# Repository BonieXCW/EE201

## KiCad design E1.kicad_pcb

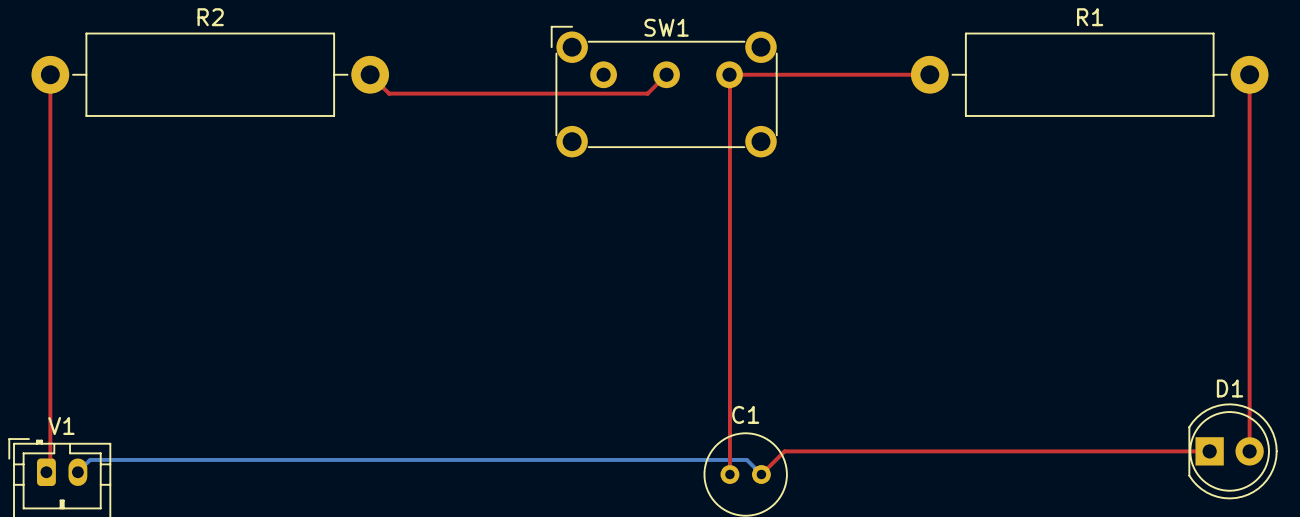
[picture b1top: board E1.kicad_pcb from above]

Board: 2 copper layers, 6 parts (0 on the bottom side), 5 nets.

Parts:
C1: 4.7 uF; C_Radial_D5.0mm_H5.0mm_P2.00mm
D1: LED; LED_D5.0mm
R1: 20 kohms; R_Axial_DIN0516_L15.5mm_D5.0mm_P20.32mm_Horizontal
R2: 2.2 kohms; R_Axial_DIN0516_L15.5mm_D5.0mm_P20.32mm_Horizontal
SW1: SW_SPDT; SW_E-Switch_EG1224_SPDT_Angled
V1: 9 V; JST_PH_B2B-PH-K_1x02_P2.00mm_Vertical

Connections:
unnamed: C1.1, R1.1, SW1.3 (C)
unnamed: C1.2, D1.1 (K), V1.2
unnamed: D1.2 (A), R1.2
unnamed: R2.1, V1.1
unnamed: R2.2, SW1.2 (B)

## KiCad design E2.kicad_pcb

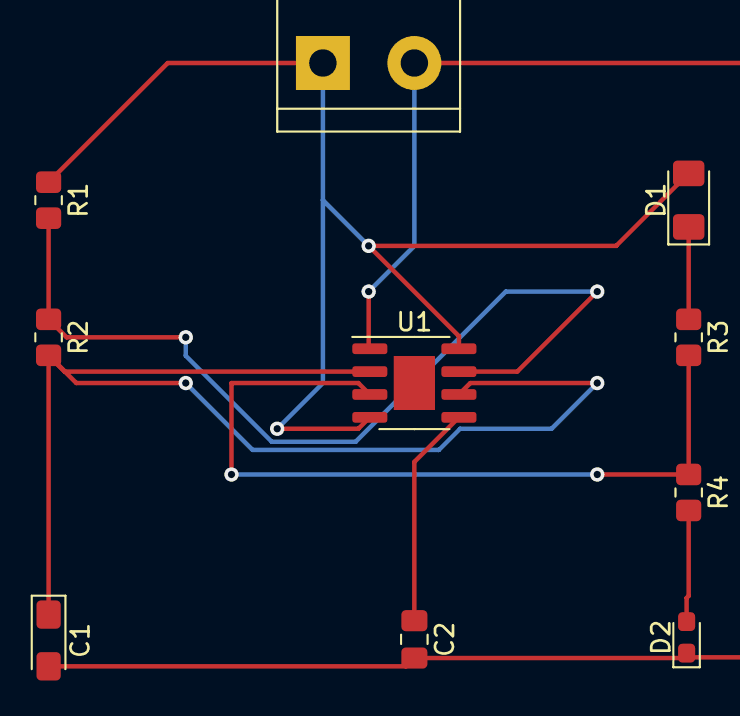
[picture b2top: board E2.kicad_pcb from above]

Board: 2 copper layers, 10 parts (0 on the bottom side), 8 nets.

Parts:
C1: 10uF; CP_EIA-3216-18_Kemet-A_Pad1.58x1.35mm_HandSolder
C2: 0.01uF; C_0805_2012Metric_Pad1.18x1.45mm_HandSolder
D1: LED; LED_1206_3216Metric_Pad1.42x1.75mm_HandSolder
D2: LED; LED_0603_1608Metric_Pad1.05x0.95mm_HandSolder
J1: Conn_01x02_Male; TerminalBlock_bornier-2_P5.08mm
R1, R3, R4: 1k; R_0805_2012Metric_Pad1.20x1.40mm_HandSolder
R2: 10k; R_0805_2012Metric_Pad1.20x1.40mm_HandSolder
U1: NE555D; SOIC-8-1EP_3.9x4.9mm_P1.27mm_EP2.29x3mm

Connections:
+9V: D1.2 (A), J1.1, R1.1, U1.4 (R), U1.8 (VCC)
/pin_2: C1.1, R2.2, U1.2 (TR), U1.6 (THR)
/pin_3: R3.2, R4.1, U1.3 (Q)
/pin_7: R1.2, R2.1, U1.7 (DIS)
GND: C1.2, C2.2, D2.1 (K), J1.2, U1.1 (GND)
unnamed: C2.1, U1.5 (CV)
unnamed: D1.1 (K), R3.1
unnamed: D2.2 (A), R4.2

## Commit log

2023-01-13 Test Markdown syntax
2023-01-13 Second test
2023-01-13 Add About Me and link to LinkedIn
2023-01-13 Deleted the unwanted line
2023-01-13 first version of my personal page
2023-01-13 adjust hobbies
2023-02-03 Create exercise1
2023-02-03 Rename exercise1.kicad_pcb to exercise1/exercise1.kicad_pcb
2023-02-03 Rename exercise1.kicad_prl to exercise1/exercise1.kicad_prl
2023-02-03 Rename exercise1.kicad_pro to exercise1/exercise1.kicad_pro
2023-02-03 Rename exercise1.kicad_sch to exercise1/exercise1.kicad_sch
2023-02-03 Rename exercise2.kicad_pcb to exercise2/exercise2.kicad_pcb
2023-02-03 Rename exercise2.kicad_prl to exercise2/exercise2.kicad_prl
2023-02-03 Rename exercise2.kicad_pro to exercise2/exercise2.kicad_pro
2023-02-03 Rename exercise2.kicad_sch to exercise2/exercise2.kicad_sch
